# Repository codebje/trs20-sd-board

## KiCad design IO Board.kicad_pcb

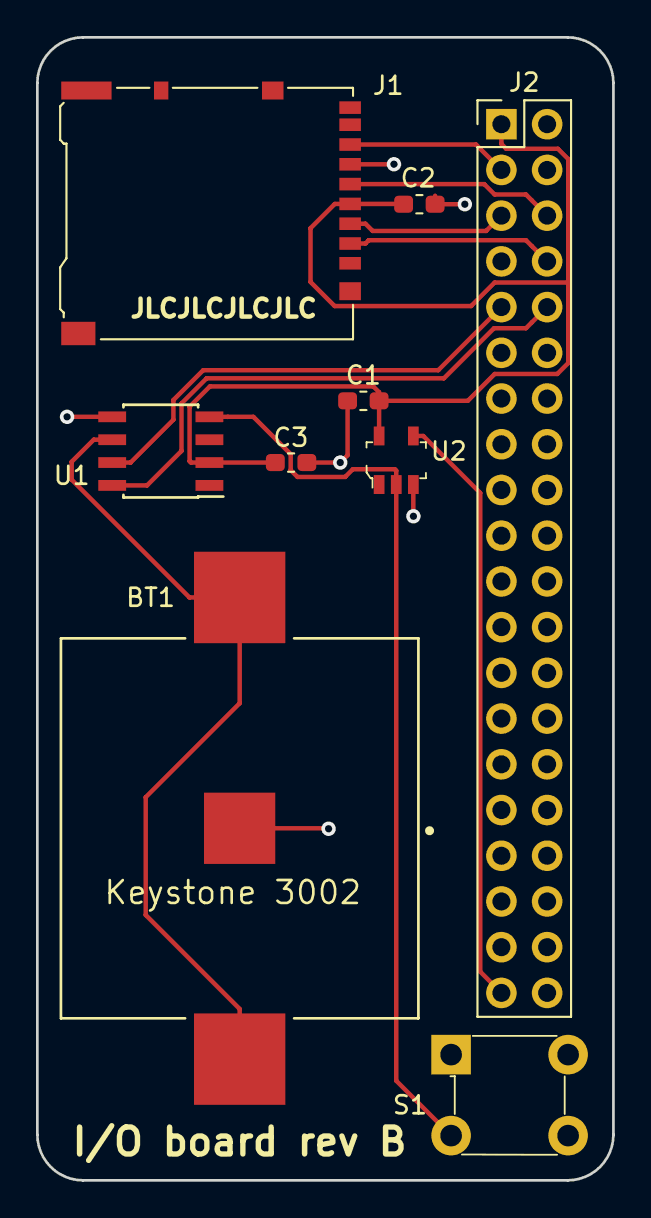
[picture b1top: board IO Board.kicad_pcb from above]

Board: 2 copper layers, 32.0 x 63.5 mm, 9 parts (0 on the bottom side), 11 nets.

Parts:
BT1: Keystone 3002; Keystone-3002TR-0
C1, C2, C3: 0.1uF; C_0603_1608Metric_Pad1.05x0.95mm_HandSolder
J1: DM3AT-SF-PEJM5; microSD_HC_Hirose_DM3AT-SF-PEJM5
J2: 2x20-pin_TRS-20_bus; PinHeader_2x20_P2.54mm_Vertical
S1: 1825910-6; Switch_Tactile_THT_6x6mm
U1: DS3232M; SOIC-8_3.9x4.9mm_P1.27mm
U2: SN74LVC1G07DBVR; SOT-753

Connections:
/3V3: C1.2, C2.2, C3.2, J1.4, J2.1, U1.2, U2.5
/SPI_CS: J1.2, J2.8
/SPI_SCK: J1.5, J2.6
/SPI_SDI: J1.7, J2.3
/SPI_SDO: J1.3, J2.5
GNDREF: BT1.2, C1.1, C2.1, C3.1, J1.6, J2.40, S1.1, U1.5, U2.3
unnamed: BT1.1, U1.6
unnamed: J2.9, U1.7
unnamed: J2.10, U1.8
unnamed: J2.39, U2.4
unnamed: S1.3, U1.4, U2.2

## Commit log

2020-11-22 Begin an I/O board
2020-11-23 rev A
2020-12-05 check twice, fab once
